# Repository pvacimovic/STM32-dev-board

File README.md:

# STM32-dev-board
Custom PCB design. KiCad was used for designing.

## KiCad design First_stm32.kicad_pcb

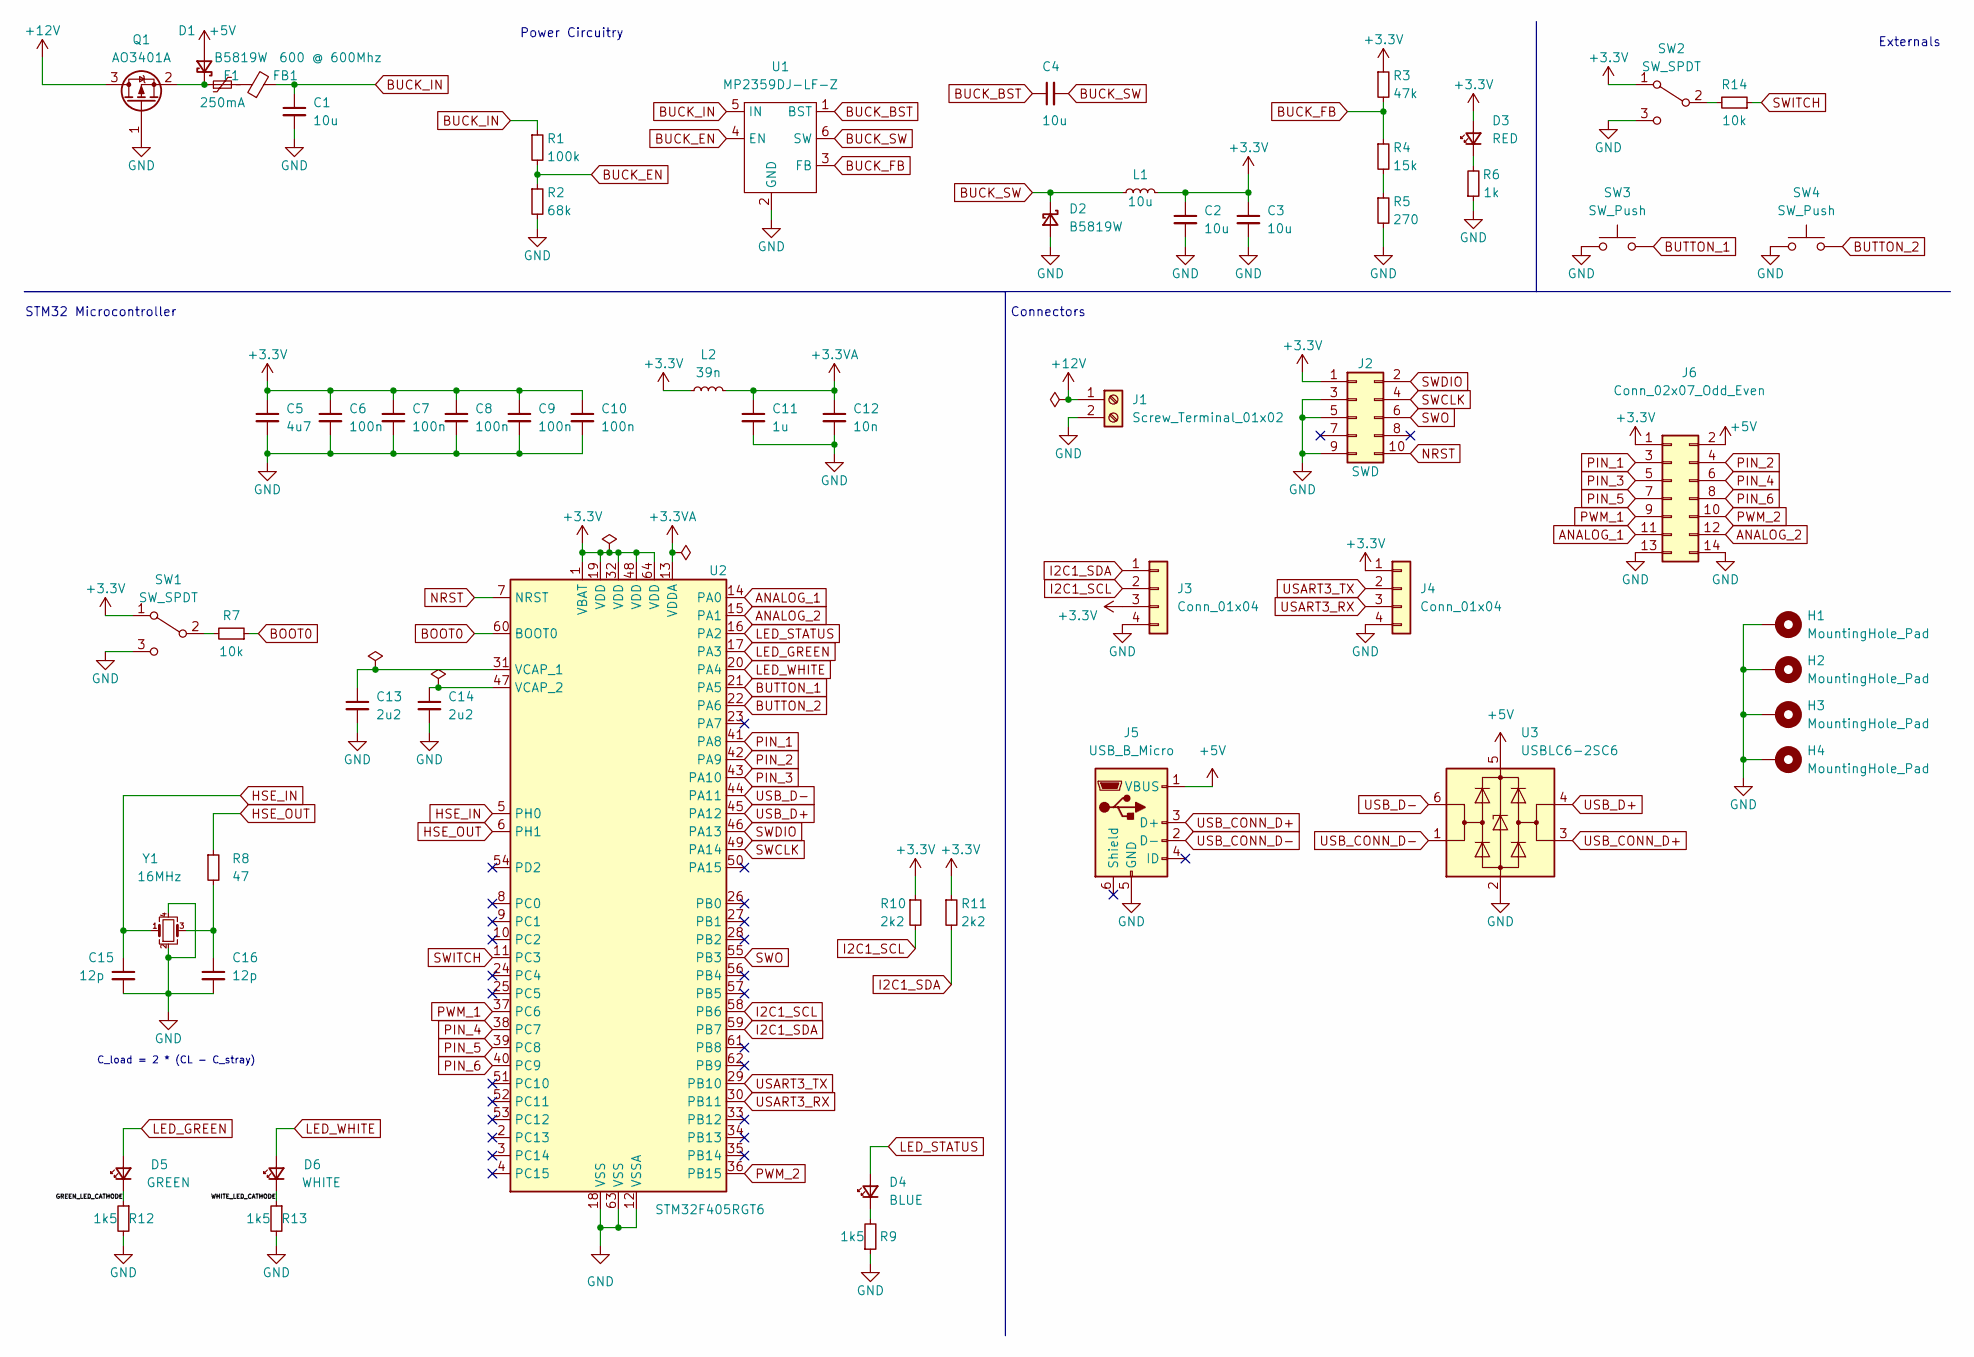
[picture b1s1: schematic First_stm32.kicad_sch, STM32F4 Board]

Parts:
C1, C2, C3: 10u; C_1206_3216Metric; LCSC Part # C13585
C4: 10u; C_0603_1608Metric; LCSC Part # C57112
C5: 4u7; C_0603_1608Metric; LCSC Part # C19666
C6, C7, C8, C9, C10: 100n; C_0402_1005Metric; LCSC Part # C1525
C11: 1u; C_0402_1005Metric; LCSC Part # C52923
C12: 10n; C_0402_1005Metric; LCSC Part # C15195
C13, C14: 2u2; C_0603_1608Metric; LCSC Part # C23630
C15, C16: 12p; C_0402_1005Metric; LCSC Part # C1547
D1, D2: B5819W; D_SOD-123; LCSC Part # C8598
D3: RED; LED_0603_1608Metric; LCSC Part # C2286
D4: BLUE; LED_0603_1608Metric; LCSC Part # C72041
D5: GREEN; LED_0603_1608Metric; LCSC Part # C72043
D6: WHITE; LED_0603_1608Metric; LCSC Part # C2290
F1: 250mA; Fuse_1206_3216Metric; LCSC Part # C369159
FB1: 600 @ 600Mhz; L_0805_2012Metric; LCSC Part # C1017
H1, H2, H3, H4: MountingHole_Pad; MountingHole_4.3mm_M4_Pad_Via
J1: Screw_Terminal_01x02; TerminalBlock_Phoenix_PT-1,5-2-5.0-H_1x02_P5.00mm_Horizontal; LCSC Part # C91153
J2: SWD; PinSocket_2x05_P2.54mm_Vertical
J3, J4: Conn_01x04; PinSocket_1x04_P2.54mm_Vertical
J5: USB_B_Micro; USB_Micro-B_Molex_47346-0001; LCSC Part # C132560
J6: Conn_02x07_Odd_Even; PinSocket_2x07_P2.54mm_Vertical
L1: 10u; Inductor_Petar; LCSC Part # C328252
L2: 39n; L_0402_1005Metric; LCSC Part # C26443
Q1: AO3401A; SOT-23; LCSC Part # C15127
R1: 100k; R_0603_1608Metric; LCSC Part # C25803
R2: 68k; R_0603_1608Metric; LCSC Part # C23231
R3: 47k; R_0603_1608Metric; LCSC Part # C25819
R4: 15k; R_0603_1608Metric; LCSC Part # C22809
R5: 270; R_0603_1608Metric; LCSC Part # C22966
R6: 1k; R_0603_1608Metric; LCSC Part # C21190
R7, R14: 10k; R_0402_1005Metric; LCSC Part # C25744
R8: 47; R_0402_1005Metric; LCSC Part # C25118
R9, R12, R13: 1k5; R_0603_1608Metric; LCSC Part # C22843
R10, R11: 2k2; R_0402_1005Metric; LCSC Part # C25879
SW1, SW2: SW_SPDT; Switch_Petar; LCSC Part # C431541
SW3, SW4: SW_Push; Push_Button_Petar; LCSC Part # C108650
U1: MP2359DJ-LF-Z; SOT-23-6; LCSC Part # C2959845
U2: STM32F405RGT6; LQFP-64_10x10mm_P0.5mm; LCSC Part # C15742
U3: USBLC6-2SC6; SOT-23-6; LCSC Part # C7519
Y1: 16MHz; Crystal_SMD_3225-4Pin_3.2x2.5mm; LCSC Part # C13738

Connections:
+3.3V: C2.1, C3.1, C5.1, C6.1, C7.1, C8.1, C9.1, C10.1, D3.2 (A), J2.1, J3.3, J4.1, J6.1, L1.2, L2.1, R3.1, R10.1, R11.1, SW1.1 (A), SW2.1 (A), U2.1 (VBAT), U2.19 (VDD), U2.32 (VDD), U2.48 (VDD), U2.64 (VDD)
+3.3VA: C11.1, C12.1, L2.2, U2.13 (VDDA)
+5V: D1.2 (A), J5.1 (VBUS), J6.2, U3.5 (VBUS)
+12V: J1.1, Q1.3 (D)
/GREEN_LED_CATHODE: D5.1 (K), R12.1
/WHITE_LED_CATHODE: D6.1 (K), R13.1
ANALOG_1: J6.11, U2.14 (PA0)
ANALOG_2: J6.12, U2.15 (PA1)
BOOT0: R7.1, U2.60 (BOOT0)
BUCK_BST: C4.1, U1.1 (BST)
BUCK_EN: R1.2, R2.1, U1.4 (EN)
BUCK_FB: R3.2, R4.1, U1.3 (FB)
BUCK_IN: C1.1, FB1.2, R1.1, U1.5 (IN)
BUCK_SW: C4.2, D2.1 (K), L1.1, U1.6 (SW)
BUTTON_1: SW3.2, U2.21 (PA5)
BUTTON_2: SW4.2, U2.22 (PA6)
GND: C1.2, C2.2, C3.2, C5.2, C6.2, C7.2, C8.2, C9.2, C10.2, C11.2, C12.2, C13.2, C14.2, C15.2, C16.2, D2.2 (A), H1.1, H2.1, H3.1, H4.1, J1.2, J2.3, J2.5, J2.9, J3.4, J4.4, J5.5 (GND), J6.13, J6.14, Q1.1 (G), R2.2, R5.2, R6.1, R9.1, R12.2, R13.2, SW1.3 (C), SW2.3 (C), SW3.1, SW4.1, U1.2 (GND), U2.12 (VSSA), U2.18 (VSS), U2.63 (VSS), U3.2 (GND), Y1.2, Y1.4
HSE_IN: C15.1, U2.5 (PH0), Y1.1
HSE_OUT: R8.1, U2.6 (PH1)
I2C1_SCL: J3.2, R10.2, U2.58 (PB6)
I2C1_SDA: J3.1, R11.2, U2.59 (PB7)
LED_GREEN: D5.2 (A), U2.17 (PA3)
LED_STATUS: D4.2 (A), U2.16 (PA2)
LED_WHITE: D6.2 (A), U2.20 (PA4)
NRST: J2.10, U2.7 (NRST)
unnamed: C13.1, U2.31 (VCAP_1)
unnamed: C14.1, U2.47 (VCAP_2)
unnamed: C16.1, R8.2, Y1.3
unnamed: D1.1 (K), F1.1, Q1.2 (S)
unnamed: D3.1 (K), R6.2
unnamed: D4.1 (K), R9.2
unnamed: F1.2, FB1.1
unnamed: R4.2, R5.1
unnamed: R7.2, SW1.2 (B)
unnamed: R14.2, SW2.2 (B)
PIN_1: J6.3, U2.41 (PA8)
PIN_2: J6.4, U2.42 (PA9)
PIN_3: J6.5, U2.43 (PA10)
PIN_4: J6.6, U2.38 (PC7)
PIN_5: J6.7, U2.39 (PC8)
PIN_6: J6.8, U2.40 (PC9)
PWM_1: J6.9, U2.37 (PC6)
PWM_2: J6.10, U2.36 (PB15)
SWCLK: J2.4, U2.49 (PA14)
SWDIO: J2.2, U2.46 (PA13)
SWITCH: R14.1, U2.11 (PC3)
SWO: J2.6, U2.55 (PB3)
USART3_RX: J4.3, U2.30 (PB11)
USART3_TX: J4.2, U2.29 (PB10)
USB_CONN_D+: J5.3 (D+), U3.3 (I/O2)
USB_CONN_D-: J5.2 (D-), U3.1 (I/O1)
USB_D+: U2.45 (PA12), U3.4 (I/O2)
USB_D-: U2.44 (PA11), U3.6 (I/O1)

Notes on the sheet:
Power Circuitry
C_load = 2 * (CL - C_stray)
Connectors
Externals
STM32 Microcontroller

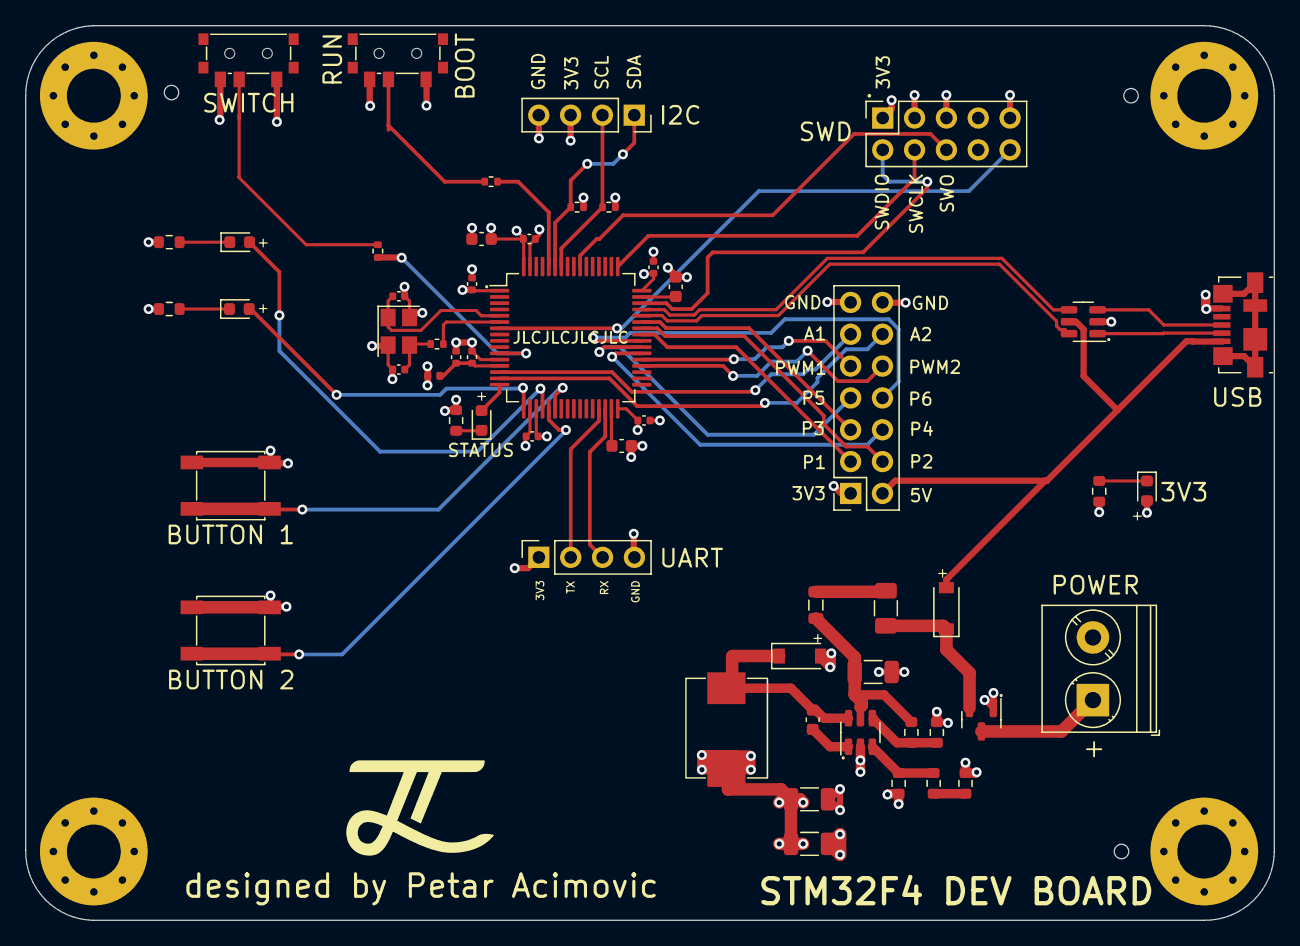
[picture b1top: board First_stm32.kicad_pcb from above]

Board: 4 copper layers, 99.6 x 71.4 mm, 59 parts (0 on the bottom side), 53 nets.

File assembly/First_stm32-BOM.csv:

Comment,Designator,Footprint,LCSC Part #
"10u","C1,C2,C3","C_1206_3216Metric","C13585"
"10u","C4","C_0603_1608Metric","C57112"
"4u7","C5","C_0603_1608Metric","C19666"
"100n","C6,C7,C8,C9,C10","C_0402_1005Metric","C1525"
"1u","C11","C_0402_1005Metric","C52923"
"10n",C12,"C_0402_1005Metric","C15195"
"2u2","C13,C14","C_0603_1608Metric","C23630"
"12p","C15,C16","C_0402_1005Metric","C1547"
"B5819W","D1,D2","D_SOD-123","C8598"
"RED","D3","LED_0603_1608Metric","C2286"
"BLUE","D4","LED_0603_1608Metric","C72041"
"GREEN","D5","LED_0603_1608Metric","C72043"
"WHITE","D6","LED_0603_1608Metric","C2290"
"250mA","F1","Fuse_1206_3216Metric","C369159"
"600 @ 600Mhz","FB1","L_0805_2012Metric","C1017"
"MountingHole_Pad","H1,H2,H3,H4","MountingHole_4.3mm_M4_Pad_Via",
"Screw_Terminal_01x02","J1","TerminalBlock_Phoenix_PT-1,5-2-5.0-H_1x02_P5.00mm_Horizontal","C91153"
"SWD","J2","PinSocket_2x05_P2.54mm_Vertical",
"Conn_01x04","J3,J4","PinSocket_1x04_P2.54mm_Vertical",
"USB_B_Micro","J5","USB_Micro-B_Molex_47346-0001","C132560"
"Conn_02x07_Odd_Even","J6",PinSocket_2x07_P2.54mm_Vertical,
"10u","L1","Inductor_Petar","C328252"
"39n","L2","L_0402_1005Metric","C26443"
"AO3401A","Q1","SOT-23","C15127"
"100k","R1","R_0603_1608Metric","C25803"
"68k","R2","R_0603_1608Metric","C23231"
"47k","R3","R_0603_1608Metric","C25819"
"15k","R4","R_0603_1608Metric","C22809"
"270","R5","R_0603_1608Metric","C22966"
"1k","R6","R_0603_1608Metric","C21190"
"10k","R7,R14","R_0402_1005Metric","C25744"
"47","R8","R_0402_1005Metric","C25118"
"2k2","R10,R11","R_0402_1005Metric","C25879"
"1k5","R9,R12,R13","R_0603_1608Metric","C22843"
"SW_SPDT","SW1,SW2","Switch_Petar","C431541"
"SW_Push","SW3,SW4","Push_Button_Petar","C108650"
"MP2359DJ-LF-Z","U1","SOT-23-6","C2959845"
"STM32F405RGT6","U2","LQFP-64_10x10mm_P0.5mm","C15742"
"USBLC6-2SC6","U3","SOT-23-6","C7519"
"16MHz","Y1","Crystal_SMD_3225-4Pin_3.2x2.5mm","C13738"
